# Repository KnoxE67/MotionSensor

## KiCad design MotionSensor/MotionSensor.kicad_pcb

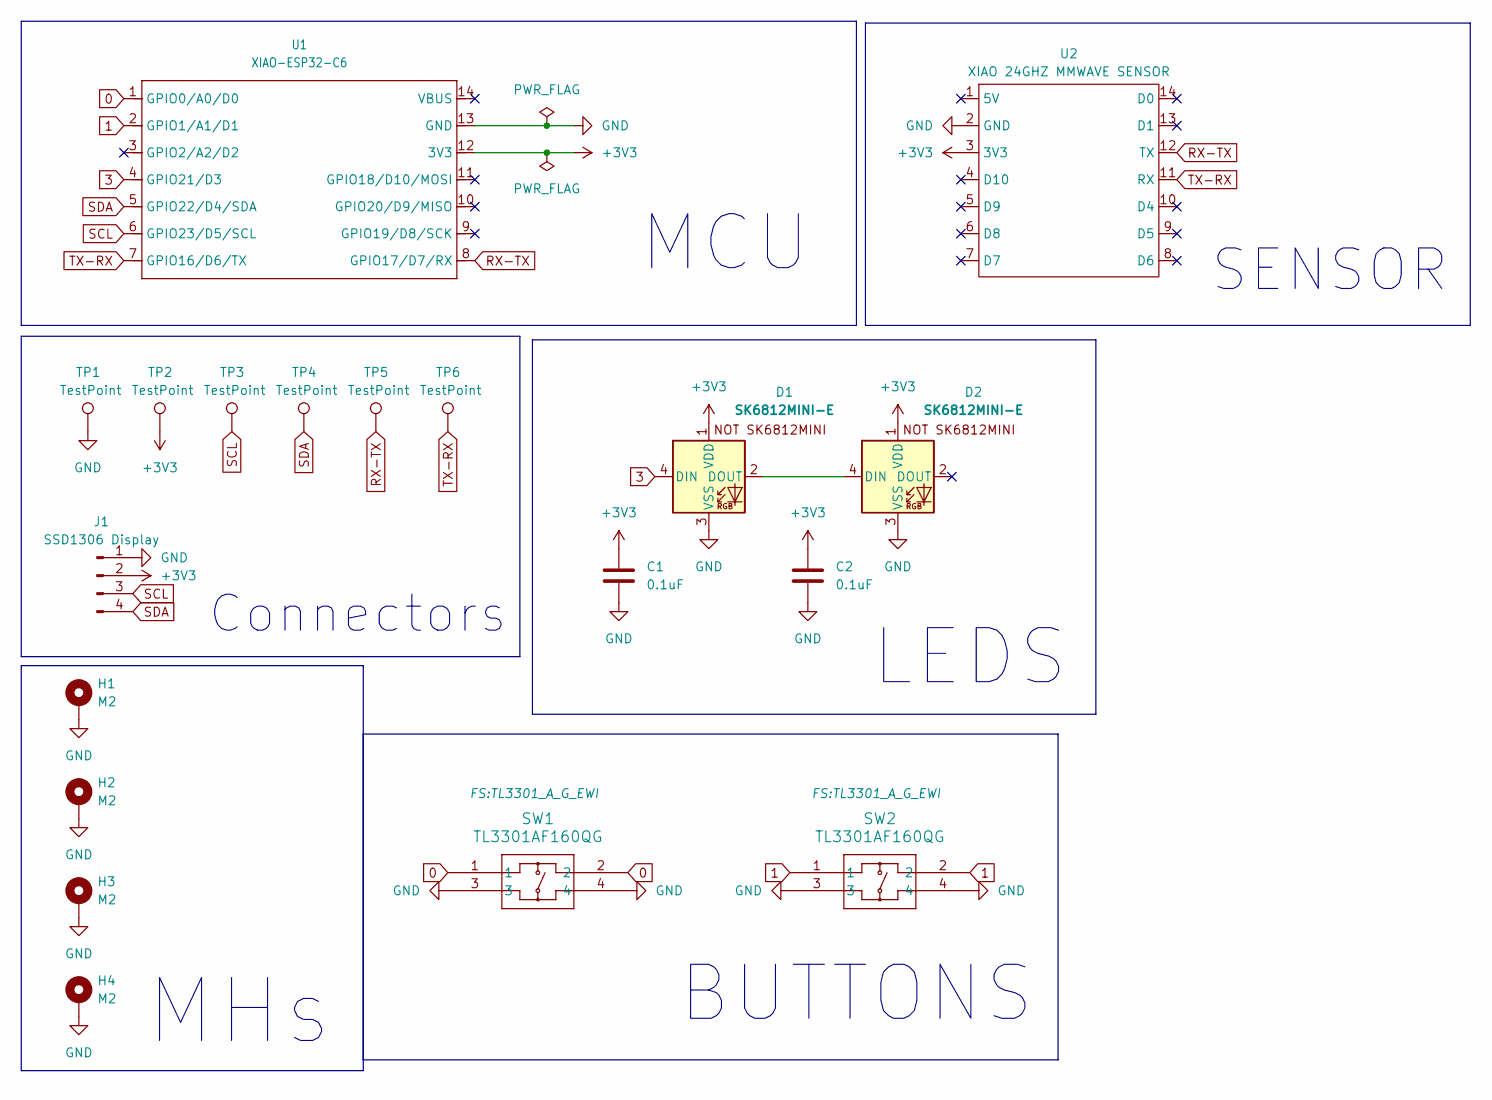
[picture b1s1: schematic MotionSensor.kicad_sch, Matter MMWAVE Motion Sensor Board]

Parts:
C1, C2: 0.1uF; C_0603_1608Metric_Pad1.08x0.95mm_HandSolder
D1, D2: SK6812MINI-E; SK6812MINI-E_fixed
H1, H2, H3, H4: M2; MountingHole_2.2mm_M2_Pad
J1: SSD1306 Display; SSD1306-0.91-OLED-4pin-128x32
SW1, SW2: TL3301AF160QG; TL3301_A_G_EWI
TP1, TP2, TP3, TP4, TP5, TP6: TestPoint; TestPoint_Pad_2.0x2.0mm
U1: XIAO-ESP32-C6; XIAO-ESP32-C6-DIP
U2: XIAO 24GHZ MMWAVE SENSOR; XIAO-14P-Add-On

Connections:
0: SW1.1, SW1.2, U1.1 (GPIO0/A0/D0)
1: SW2.1, SW2.2, U1.2 (GPIO1/A1/D1)
3: D1.4 (DIN), U1.4 (GPIO21/D3)
+3V3: C1.1, C2.1, D1.1 (VDD), D2.1 (VDD), J1.2, TP2.1 (1_1), U1.12 (3V3), U2.3 (3V3)
GND: C1.2, C2.2, D1.3 (VSS), D2.3 (VSS), H1.1 (1_1), H2.1 (1_1), H3.1 (1_1), H4.1 (1_1), J1.1, SW1.3, SW1.4, SW2.3, SW2.4, TP1.1 (1_1), U1.13 (GND), U2.2 (GND)
unnamed: D1.2 (DOUT), D2.4 (DIN)
RX-TX: TP5.1 (1_1), U1.8 (GPIO17/D7/RX), U2.12 (TX)
SCL: J1.3, TP3.1 (1_1), U1.6 (GPIO23/D5/SCL)
SDA: J1.4, TP4.1 (1_1), U1.5 (GPIO22/D4/SDA)
TX-RX: TP6.1 (1_1), U1.7 (GPIO16/D6/TX), U2.11 (RX)

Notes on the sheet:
SENSOR
MCU
LEDS
MHs
Connectors
BUTTONS

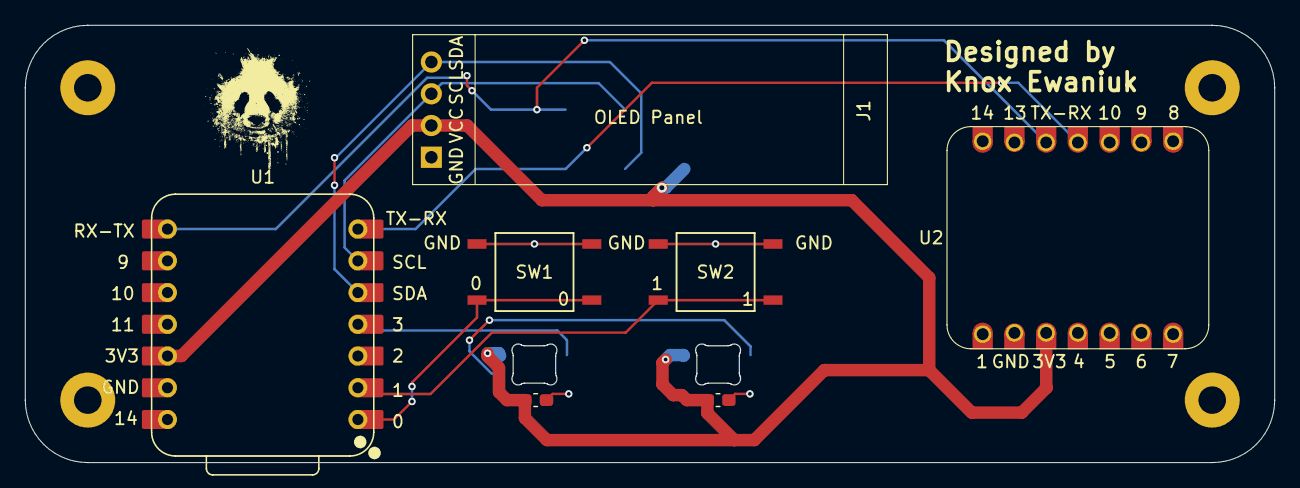
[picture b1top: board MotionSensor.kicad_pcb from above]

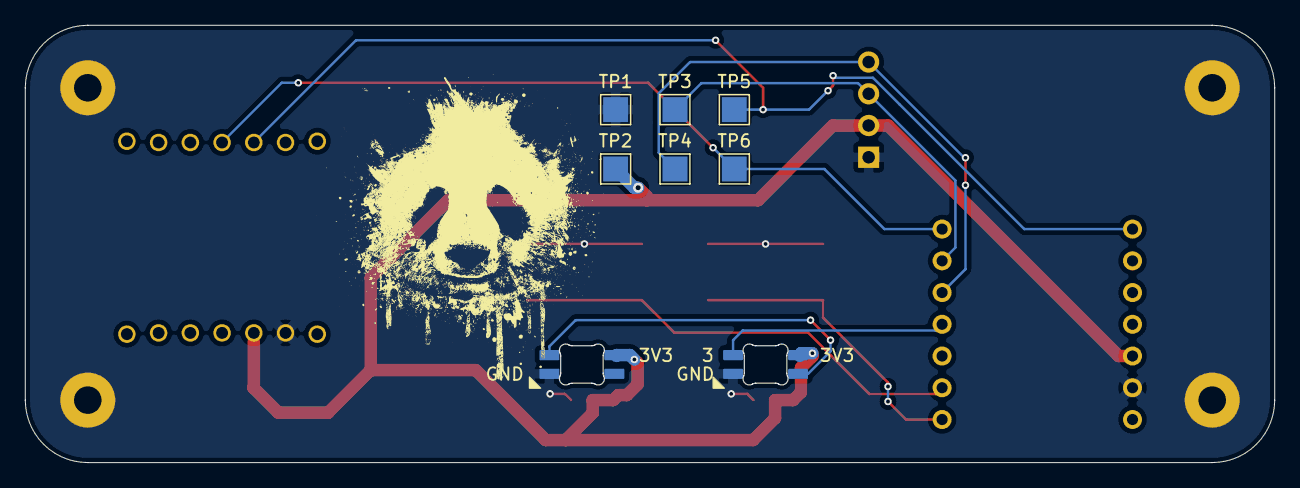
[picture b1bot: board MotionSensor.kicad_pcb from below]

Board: 2 copper layers, 100.0 x 35.0 mm, 19 parts (6 on the bottom side), 10 nets.
